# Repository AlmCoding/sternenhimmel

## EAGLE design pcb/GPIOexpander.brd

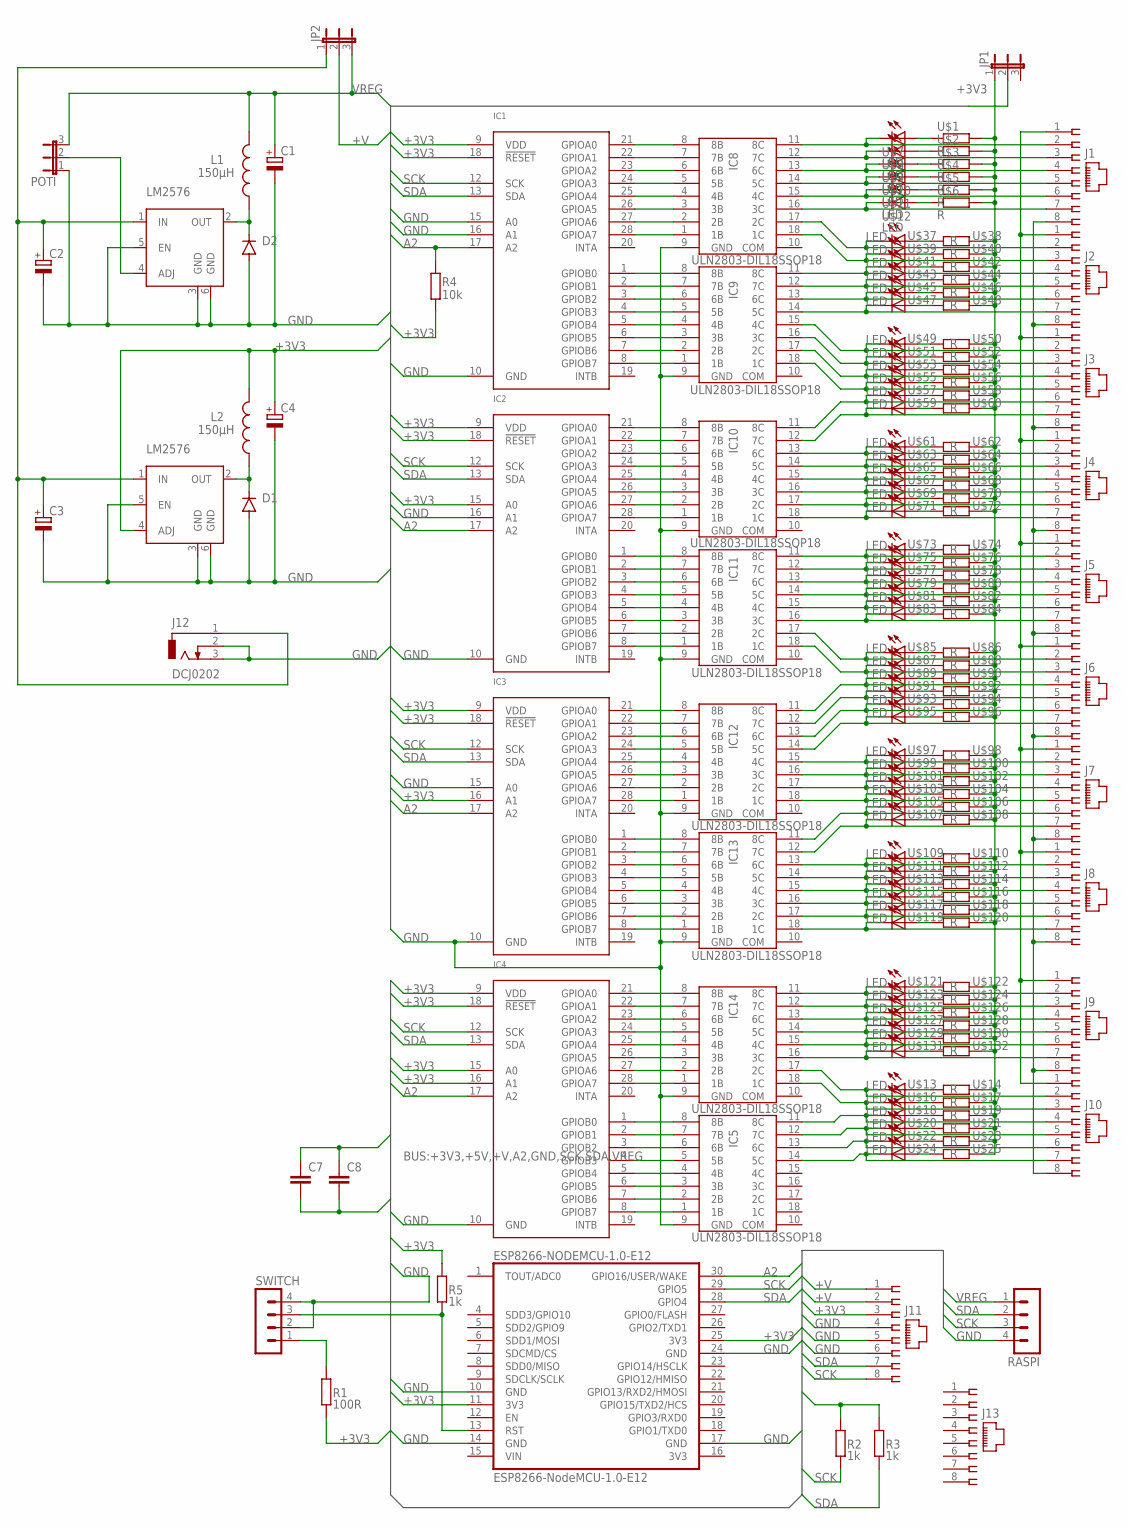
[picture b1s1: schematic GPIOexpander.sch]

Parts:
C1, C2, C3, C4: CPOL-EUE5-10.5; E5-10,5
C7, C8: C-EUC0805; C0805
D1, D2: DIODE-SMB; SMB
ESP8266-NODEMCU-1.0-E12: ESP8266-NodeMCU-1.0-E12; MCP8266-MODULE
IC1, IC2, IC3, IC4: MCP23017-DIL28-3SSOP28; SO28W
IC5, IC8, IC9, IC10, IC11, IC12, IC13, IC14: ULN2803-DIL18SSOP18; SO18W
J1, J2, J3, J4, J5, J6, J7, J8, J9, J10, J11, J13: 215877-7
J12: DCJ0202; DCJ0303
JP1, JP2: JP2E; JP2
L1, L2: 150µH; BIG_COIL
POTI: JP2E; JP2
R1: 100R; C0805
R2, R3, R5: 1k; C0805
R4: 10k; C0805
RASPI: MA04-1
SWITCH: MA04-1
U$1, U$2, U$3, U$4, U$5, U$6, U$14, U$17, U$19, U$21, U$23, U$25, U$38, U$40, U$42, U$44, U$46, U$48, U$50, U$52, U$54, U$56, U$58, U$60, U$62, U$64, U$66, U$68, U$70, U$72, U$74, U$76, U$78, U$80, U$82, U$84, U$86, U$88, U$90, U$92, U$94, U$96, U$98, U$100, U$102, U$104, U$106, U$108, U$110, U$112, U$114, U$116, U$118, U$120, U$122, U$124, U$126, U$128, U$130, U$132: R; C0805
U$7, U$8, U$9, U$10, U$11, U$12, U$13, U$16, U$18, U$20, U$22, U$24, U$37, U$39, U$41, U$43, U$45, U$47, U$49, U$51, U$53, U$55, U$57, U$59, U$61, U$63, U$65, U$67, U$69, U$71, U$73, U$75, U$77, U$79, U$81, U$83, U$85, U$87, U$89, U$91, U$93, U$95, U$97, U$99, U$101, U$103, U$105, U$107, U$109, U$111, U$113, U$115, U$117, U$119, U$121, U$123, U$125, U$127, U$129, U$131: LED; C0805
U$26, U$28: LM2576; D2PAK

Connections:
+3V3: C4.+, C7.1, C8.1, ESP8266-NODEMCU-1.0-E12.11 (3V3), ESP8266-NODEMCU-1.0-E12.25 (3V3), IC1.9 (VDD), IC1.18 (!RESET), IC2.9 (VDD), IC2.15 (A0), IC2.18 (!RESET), IC3.9 (VDD), IC3.16 (A1), IC3.18 (!RESET), IC4.9 (VDD), IC4.15 (A0), IC4.16 (A1), IC4.18 (!RESET), J11.3, JP1.2, L2.P$2 (2), R1.1, R2.2, R3.2, R4.1, R5.2, U$28.4 (ADJ)
+V: J1.1, J2.1, J3.1, J4.1, J5.1, J6.1, J7.1, J8.1, J9.1, J10.1, J11.1, J11.2, JP2.2
A2: ESP8266-NODEMCU-1.0-E12.30 (GPIO16/USER/WAKE), IC1.17 (A2), IC2.17 (A2), IC3.17 (A2), IC4.17 (A2), R4.2
GND: C1.-, C2.-, C3.-, C4.-, C7.2, C8.2, D1.A, D2.A, ESP8266-NODEMCU-1.0-E12.10 (GND), ESP8266-NODEMCU-1.0-E12.14 (GND), ESP8266-NODEMCU-1.0-E12.17 (GND), ESP8266-NODEMCU-1.0-E12.24 (GND), IC1.10 (GND), IC1.15 (A0), IC1.16 (A1), IC2.10 (GND), IC2.16 (A1), IC3.10 (GND), IC3.15 (A0), IC4.10 (GND), IC5.9 (GND), IC8.9 (GND), IC9.9 (GND), IC10.9 (GND), IC11.9 (GND), IC12.9 (GND), IC13.9 (GND), IC14.9 (GND), J1.8, J2.8, J3.8, J4.8, J5.8, J6.8, J7.8, J8.8, J9.8, J10.8, J11.4, J11.5, J11.6, J12.2, J12.3, POTI.1, RASPI.4, SWITCH.2, SWITCH.4, U$26.3 (GND), U$26.5 (EN), U$26.6 (GND), U$28.3 (GND), U$28.5 (EN), U$28.6 (GND)
unnamed: IC1.21 (GPIOA0), IC8.8 (8B)
unnamed: IC1.22 (GPIOA1), IC8.7 (7B)
unnamed: IC1.23 (GPIOA2), IC8.6 (6B)
unnamed: IC1.24 (GPIOA3), IC8.5 (5B)
unnamed: IC1.25 (GPIOA4), IC8.4 (4B)
unnamed: IC1.26 (GPIOA5), IC8.3 (3B)
unnamed: IC1.27 (GPIOA6), IC8.2 (2B)
unnamed: IC1.28 (GPIOA7), IC8.1 (1B)
unnamed: IC4.8 (GPIOB7), IC5.1 (1B)
unnamed: IC1.1 (GPIOB0), IC9.8 (8B)
unnamed: IC1.2 (GPIOB1), IC9.7 (7B)
unnamed: IC1.3 (GPIOB2), IC9.6 (6B)
unnamed: IC1.4 (GPIOB3), IC9.5 (5B)
unnamed: IC1.5 (GPIOB4), IC9.4 (4B)
unnamed: IC1.6 (GPIOB5), IC9.3 (3B)
unnamed: IC1.7 (GPIOB6), IC9.2 (2B)
unnamed: IC1.8 (GPIOB7), IC9.1 (1B)
unnamed: IC4.7 (GPIOB6), IC5.2 (2B)
unnamed: IC2.21 (GPIOA0), IC10.8 (8B)
unnamed: IC2.22 (GPIOA1), IC10.7 (7B)
unnamed: IC2.23 (GPIOA2), IC10.6 (6B)
unnamed: IC2.24 (GPIOA3), IC10.5 (5B)
unnamed: IC2.25 (GPIOA4), IC10.4 (4B)
unnamed: IC2.26 (GPIOA5), IC10.3 (3B)
unnamed: IC2.27 (GPIOA6), IC10.2 (2B)
unnamed: IC2.28 (GPIOA7), IC10.1 (1B)
unnamed: IC4.6 (GPIOB5), IC5.3 (3B)
unnamed: IC2.1 (GPIOB0), IC11.8 (8B)
unnamed: IC2.2 (GPIOB1), IC11.7 (7B)
unnamed: IC2.3 (GPIOB2), IC11.6 (6B)
unnamed: IC2.4 (GPIOB3), IC11.5 (5B)
unnamed: IC2.5 (GPIOB4), IC11.4 (4B)
unnamed: IC2.6 (GPIOB5), IC11.3 (3B)
unnamed: IC2.7 (GPIOB6), IC11.2 (2B)
unnamed: IC2.8 (GPIOB7), IC11.1 (1B)
unnamed: IC9.15 (4C), J3.2, U$49.2 (C)
unnamed: IC3.21 (GPIOA0), IC12.8 (8B)
unnamed: IC3.22 (GPIOA1), IC12.7 (7B)
unnamed: IC3.23 (GPIOA2), IC12.6 (6B)
unnamed: IC3.24 (GPIOA3), IC12.5 (5B)
unnamed: IC3.25 (GPIOA4), IC12.4 (4B)
unnamed: IC3.26 (GPIOA5), IC12.3 (3B)
unnamed: IC3.27 (GPIOA6), IC12.2 (2B)
unnamed: IC3.28 (GPIOA7), IC12.1 (1B)
unnamed: IC9.16 (3C), J3.3, U$51.2 (C)
unnamed: IC3.1 (GPIOB0), IC13.8 (8B)
unnamed: IC3.2 (GPIOB1), IC13.7 (7B)
unnamed: IC3.3 (GPIOB2), IC13.6 (6B)
unnamed: IC3.4 (GPIOB3), IC13.5 (5B)
unnamed: IC3.5 (GPIOB4), IC13.4 (4B)
unnamed: IC3.6 (GPIOB5), IC13.3 (3B)
unnamed: IC3.7 (GPIOB6), IC13.2 (2B)
unnamed: IC3.8 (GPIOB7), IC13.1 (1B)
unnamed: IC9.17 (2C), J3.4, U$53.2 (C)
unnamed: IC4.21 (GPIOA0), IC14.8 (8B)
unnamed: IC4.22 (GPIOA1), IC14.7 (7B)
unnamed: IC4.23 (GPIOA2), IC14.6 (6B)
unnamed: IC4.24 (GPIOA3), IC14.5 (5B)
unnamed: IC4.25 (GPIOA4), IC14.4 (4B)
unnamed: IC4.26 (GPIOA5), IC14.3 (3B)
unnamed: IC4.27 (GPIOA6), IC14.2 (2B)
unnamed: IC4.28 (GPIOA7), IC14.1 (1B)
unnamed: IC8.17 (2C), J2.2, U$37.2 (C)
unnamed: IC4.5 (GPIOB4), IC5.4 (4B)
unnamed: IC4.4 (GPIOB3), IC5.5 (5B)
unnamed: IC4.3 (GPIOB2), IC5.6 (6B)
unnamed: IC4.2 (GPIOB1), IC5.7 (7B)
unnamed: IC4.1 (GPIOB0), IC5.8 (8B)
unnamed: IC14.17 (2C), J10.2, U$13.2 (C)
unnamed: JP1.1, U$1.2, U$2.2, U$3.2, U$4.2, U$5.2, U$6.2, U$14.2, U$17.2, U$19.2, U$21.2, U$23.2, U$25.2, U$38.2, U$40.2, U$42.2, U$44.2, U$46.2, U$48.2, U$50.2, U$52.2, U$54.2, U$56.2, U$58.2, U$60.2, U$62.2, U$64.2, U$66.2, U$68.2, U$70.2, U$72.2, U$74.2, U$76.2, U$78.2, U$80.2, U$82.2, U$84.2, U$86.2, U$88.2, U$90.2, U$92.2, U$94.2, U$96.2, U$98.2, U$100.2, U$102.2, U$104.2, U$106.2, U$108.2, U$110.2, U$112.2, U$114.2, U$116.2, U$118.2, U$120.2, U$122.2, U$124.2, U$126.2, U$128.2, U$130.2, U$132.2
unnamed: D2.C, L1.P$1 (1), U$26.2 (OUT)
unnamed: IC8.11 (8C), J1.2, U$7.2 (C)
unnamed: C2.+, C3.+, J12.1, JP2.1, U$26.1 (IN), U$28.1 (IN)
unnamed: IC14.18 (1C), J10.3, U$16.2 (C)
unnamed: IC5.11 (8C), J10.4, U$18.2 (C)
unnamed: IC5.12 (7C), J10.5, U$20.2 (C)
unnamed: IC5.13 (6C), J10.6, U$22.2 (C)
unnamed: IC5.14 (5C), J10.7, U$24.2 (C)
unnamed: U$13.1 (A), U$14.1
unnamed: U$16.1 (A), U$17.1
unnamed: IC8.18 (1C), J2.3, U$39.2 (C)
unnamed: U$18.1 (A), U$19.1
unnamed: U$20.1 (A), U$21.1
unnamed: U$22.1 (A), U$23.1
unnamed: U$24.1 (A), U$25.1
unnamed: POTI.2, U$26.4 (ADJ)
unnamed: D1.C, L2.P$1 (1), U$28.2 (OUT)
unnamed: ESP8266-NODEMCU-1.0-E12.13 (RST), R5.1, SWITCH.3
unnamed: R1.2, SWITCH.1
unnamed: IC9.12 (7C), J2.5, U$43.2 (C)
unnamed: IC9.11 (8C), J2.4, U$41.2 (C)
unnamed: IC9.18 (1C), J3.5, U$55.2 (C)
unnamed: IC10.11 (8C), J3.6, U$57.2 (C)
unnamed: IC8.12 (7C), J1.3, U$8.2 (C)
unnamed: IC8.13 (6C), J1.4, U$9.2 (C)
unnamed: IC9.13 (6C), J2.6, U$45.2 (C)
unnamed: IC9.14 (5C), J2.7, U$47.2 (C)
unnamed: IC8.14 (5C), J1.5, U$10.2 (C)
unnamed: IC8.15 (4C), J1.6, U$11.2 (C)
unnamed: IC8.16 (3C), J1.7, U$12.2 (C)
unnamed: IC10.12 (7C), J3.7, U$59.2 (C)
unnamed: IC10.13 (6C), J4.2, U$61.2 (C)
unnamed: IC10.14 (5C), J4.3, U$63.2 (C)
unnamed: IC10.15 (4C), J4.4, U$65.2 (C)
unnamed: IC10.16 (3C), J4.5, U$67.2 (C)
unnamed: IC10.17 (2C), J4.6, U$69.2 (C)
unnamed: IC10.18 (1C), J4.7, U$71.2 (C)
unnamed: IC11.14 (5C), J5.5, U$79.2 (C)
unnamed: IC11.15 (4C), J5.6, U$81.2 (C)
unnamed: IC11.16 (3C), J5.7, U$83.2 (C)
unnamed: IC11.11 (8C), J5.2, U$73.2 (C)
unnamed: IC11.12 (7C), J5.3, U$75.2 (C)
unnamed: IC11.13 (6C), J5.4, U$77.2 (C)
unnamed: IC11.17 (2C), J6.2, U$85.2 (C)
unnamed: IC11.18 (1C), J6.3, U$87.2 (C)
unnamed: IC12.11 (8C), J6.4, U$89.2 (C)
unnamed: IC12.12 (7C), J6.5, U$91.2 (C)
unnamed: IC12.13 (6C), J6.6, U$93.2 (C)
unnamed: IC12.14 (5C), J6.7, U$95.2 (C)
unnamed: IC12.15 (4C), J7.2, U$97.2 (C)
unnamed: IC12.16 (3C), J7.3, U$99.2 (C)
unnamed: IC12.17 (2C), J7.4, U$101.2 (C)
unnamed: IC12.18 (1C), J7.5, U$103.2 (C)
unnamed: IC13.11 (8C), J7.6, U$105.2 (C)
unnamed: IC13.12 (7C), J7.7, U$107.2 (C)
unnamed: IC13.13 (6C), J8.2, U$109.2 (C)
unnamed: IC13.14 (5C), J8.3, U$111.2 (C)
unnamed: IC13.15 (4C), J8.4, U$113.2 (C)
unnamed: IC13.16 (3C), J8.5, U$115.2 (C)
unnamed: IC13.17 (2C), J8.6, U$117.2 (C)
unnamed: IC13.18 (1C), J8.7, U$119.2 (C)
unnamed: IC14.11 (8C), J9.2, U$121.2 (C)
unnamed: IC14.12 (7C), J9.3, U$123.2 (C)
unnamed: IC14.13 (6C), J9.4, U$125.2 (C)
unnamed: IC14.14 (5C), J9.5, U$127.2 (C)
unnamed: IC14.15 (4C), J9.6, U$129.2 (C)
unnamed: IC14.16 (3C), J9.7, U$131.2 (C)
unnamed: U$1.1, U$7.1 (A)
unnamed: U$2.1, U$8.1 (A)
unnamed: U$3.1, U$9.1 (A)
unnamed: U$4.1, U$10.1 (A)
unnamed: U$5.1, U$11.1 (A)
unnamed: U$6.1, U$12.1 (A)
unnamed: U$37.1 (A), U$38.1
unnamed: U$39.1 (A), U$40.1
unnamed: U$41.1 (A), U$42.1
unnamed: U$43.1 (A), U$44.1
unnamed: U$45.1 (A), U$46.1
unnamed: U$47.1 (A), U$48.1
unnamed: U$49.1 (A), U$50.1
unnamed: U$51.1 (A), U$52.1
unnamed: U$53.1 (A), U$54.1
unnamed: U$55.1 (A), U$56.1
unnamed: U$57.1 (A), U$58.1
unnamed: U$59.1 (A), U$60.1
unnamed: U$61.1 (A), U$62.1
unnamed: U$63.1 (A), U$64.1
unnamed: U$65.1 (A), U$66.1
unnamed: U$67.1 (A), U$68.1
unnamed: U$69.1 (A), U$70.1
unnamed: U$71.1 (A), U$72.1
unnamed: U$73.1 (A), U$74.1
unnamed: U$75.1 (A), U$76.1
unnamed: U$77.1 (A), U$78.1
unnamed: U$79.1 (A), U$80.1
unnamed: U$81.1 (A), U$82.1
unnamed: U$83.1 (A), U$84.1
unnamed: U$85.1 (A), U$86.1
unnamed: U$87.1 (A), U$88.1
unnamed: U$89.1 (A), U$90.1
unnamed: U$91.1 (A), U$92.1
unnamed: U$93.1 (A), U$94.1
unnamed: U$95.1 (A), U$96.1
unnamed: U$97.1 (A), U$98.1
unnamed: U$99.1 (A), U$100.1
unnamed: U$101.1 (A), U$102.1
unnamed: U$103.1 (A), U$104.1
unnamed: U$105.1 (A), U$106.1
unnamed: U$107.1 (A), U$108.1
unnamed: U$109.1 (A), U$110.1
unnamed: U$111.1 (A), U$112.1
unnamed: U$113.1 (A), U$114.1
unnamed: U$115.1 (A), U$116.1
unnamed: U$117.1 (A), U$118.1
unnamed: U$119.1 (A), U$120.1
unnamed: U$121.1 (A), U$122.1
unnamed: U$123.1 (A), U$124.1
unnamed: U$125.1 (A), U$126.1
unnamed: U$127.1 (A), U$128.1
unnamed: U$129.1 (A), U$130.1
unnamed: U$131.1 (A), U$132.1
SCK: ESP8266-NODEMCU-1.0-E12.29 (GPIO5), IC1.12 (SCK), IC2.12 (SCK), IC3.12 (SCK), IC4.12 (SCK), J11.8, R2.1, RASPI.3
SDA: ESP8266-NODEMCU-1.0-E12.28 (GPIO4), IC1.13 (SDA), IC2.13 (SDA), IC3.13 (SDA), IC4.13 (SDA), J11.7, R3.1, RASPI.2
VREG: C1.+, JP2.3, L1.P$2 (2), POTI.3, RASPI.1

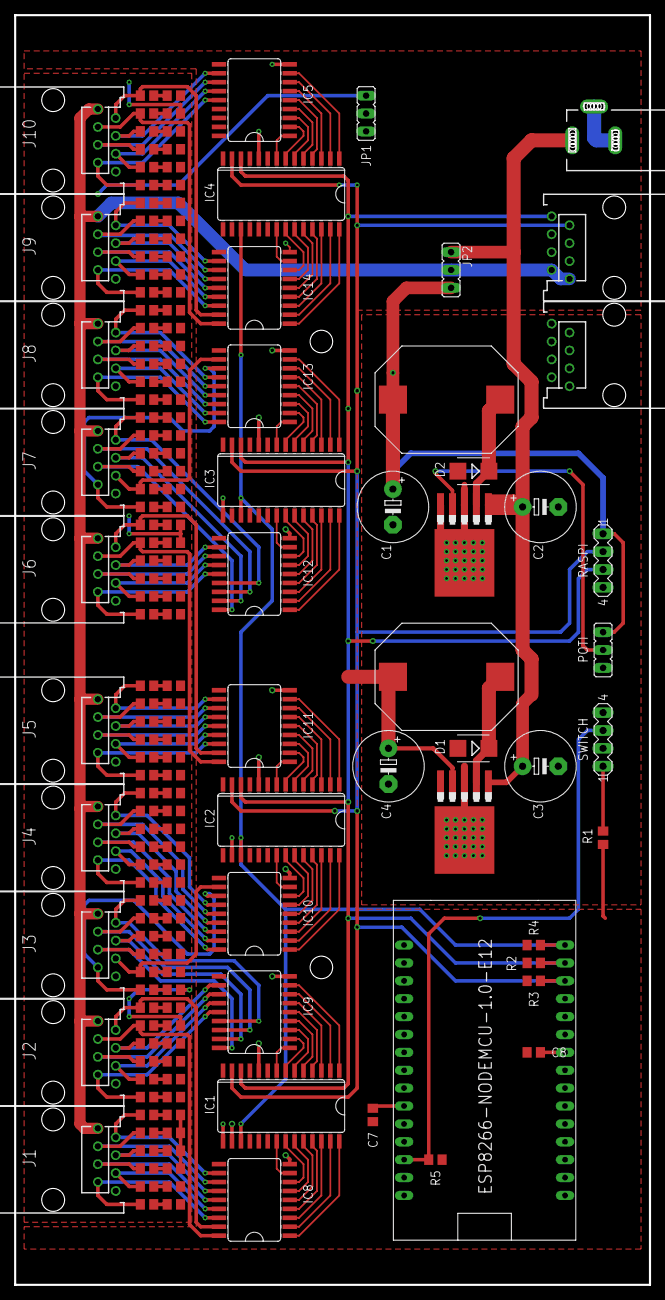
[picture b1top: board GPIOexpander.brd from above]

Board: 2 copper layers, 90.2 x 180.3 mm, 168 parts (0 on the bottom side), 198 nets.

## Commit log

2019-01-25 Init with last project state
2019-01-25 First version with 40 elements
2019-09-13 add ino
2019-09-13 add mcp23017 library
2019-09-14 add gpio expanders
2019-09-15 prog
2019-09-15 save
2019-09-15 add output transform
2019-09-29 update output trafo
2019-09-30 play show
2019-10-08 add playback
2019-10-09 finish playback
2019-10-12 fine tuning
2019-10-12 add offset, cleanup, finalize v1.0
2019-10-12 change passwd
2019-11-03 connector shift
2019-11-24 add layout
2019-11-24 clean up
2023-04-20 Refactor code
2023-04-21 Add seq parser
2023-04-22 Finish play sequence
2023-04-23 Fix step reps
2023-04-23 Add mcp simulation
2023-04-23 Reformat code
2023-04-23 Fix out2mcp pin
2023-04-23 Fix debug switch
2023-04-23 Release build
2023-04-23 Refactoring
2024-05-05 Add things
2024-12-30 Save progress
2024-12-30 Add esp32 expander
2024-12-31 port to esp32
2025-01-01 V1.0
2025-01-01 Cleanup
2025-01-02 Fix led driver vcc
2025-01-02 v2-production
2025-01-02 fix vreg on led driver
2025-01-13 Add sketch for daisy chain
2025-01-13 Add calibration values
2025-01-15 Implement Player
2025-01-16 Enable tear drops on PCB
2025-01-16 Add power test points
2025-01-23 Update PCBs
2025-01-24 Complete controller PCB v1
2025-01-24 Progress
2025-02-02 Improve thermal props
2025-02-03 Thermal refactoring
2025-02-06 Migrate to 3 chain setup
2025-02-08 Move to 3 chain setup
2025-03-05 Complete controller pcb
2025-07-18 Refactor controller pcb
2025-08-02 Fix pcb + software
2025-08-04 Write tlc class
2025-08-04 Add testpoints to pcbs
2025-08-19 Add default values + refactoring
2025-08-20 Add BLE setup
2025-08-23 Add data chunking
2025-08-25 Implement cmds
2025-08-26 Refactor config tool app
2025-08-26 Add GUI
2025-08-26 Add led changed filter on upload
2025-08-27 Add get info
2025-08-27 Build release V0.0.1
2025-08-27 Add play show to esp32 + fix python shallow copy bug
2025-08-28 Add send command feature
2025-08-28 Fix led enumeration
2025-08-28 ConfigToolApp Release V0.0.2
2025-08-28 Set idle values in config file
2025-08-29 Fix esp32 ble rx timeout bug
2025-08-29 DaisyChain Release V0.0.2
2025-08-29 Add chain statistics calculation
2025-08-30 ConfigToolApp Release V0.0.3
2025-08-30 Update led linearization gamma
2025-08-30 DaisyChain Release V0.0.3
    Add BLE OTA support
2025-08-31 Add BLE OTA to ConfigTool
2025-08-31 Add log message callback handling
2025-08-31 Speed up logging
2025-09-01 ConfigTool Release V0.0.4
    Add OTA feature
2025-09-01 Refactor class names
2025-09-01 DaisyChain V0.0.4 and ConfigTool V0.0.5 Release
2025-09-02 Release LEDpcb V0.1 and ESPpcb V0.1
2025-09-07 Run periodic chain refresh
2025-09-07 Add disable hardware option for BLE testing
2025-09-07 DaisyChain Release V0.0.5
    Add periodic chain refresh
